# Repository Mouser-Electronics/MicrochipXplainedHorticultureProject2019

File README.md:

# Microchip Xplained Horticulture Project 2019

Horticulture Sensor Project powered by:

- Microchip Xplained Board
- Mikro WiFi 3 Click Board
- Microchip ATSAMD10-based STEMMA soil moisture
- Mikro Weather Click Board temperature and humidity sensor
- DFRobots soil pH sensor
- DFRobots CO2 sensor

BOM: https://www.mouser.com/ProjectManager/ProjectDetail.aspx?AccessID=F9EF1AE298

Project Article: https://www.mouser.com/applications/smarter-green-thumb-powered-by-microchip/

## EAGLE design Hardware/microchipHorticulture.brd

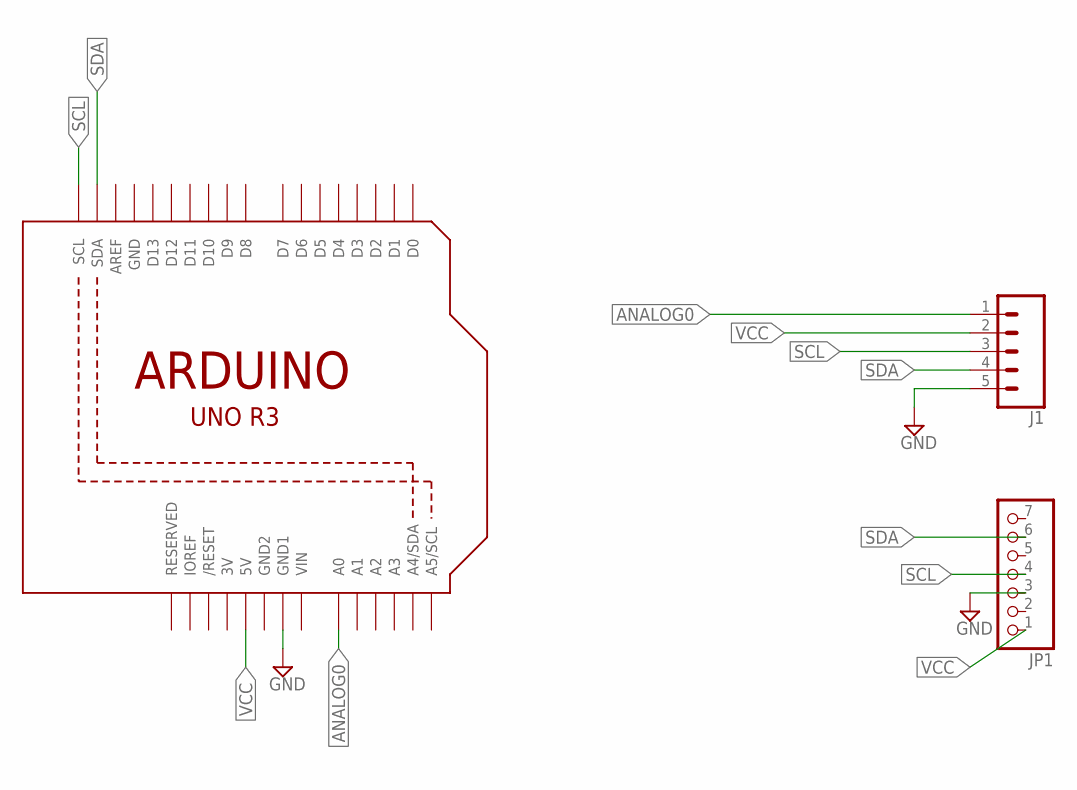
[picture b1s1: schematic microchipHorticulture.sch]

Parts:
J1: CONN_05SCREW; SCREWTERMINAL-3.5MM-5
JP1: PINHD-1X7; 1X07
U1: ARDUINOR3-BPLACE

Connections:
3V: U1.3V
ANALOG0: J1.1, U1.A0
GND: J1.5, JP1.3, U1.GND, U1.GND1
GND2: U1.GND2
SCL: J1.3, JP1.4, U1.SCL
SDA: J1.4, JP1.6, U1.SDA
VCC: J1.2, JP1.1, U1.5V
VIN: U1.VIN

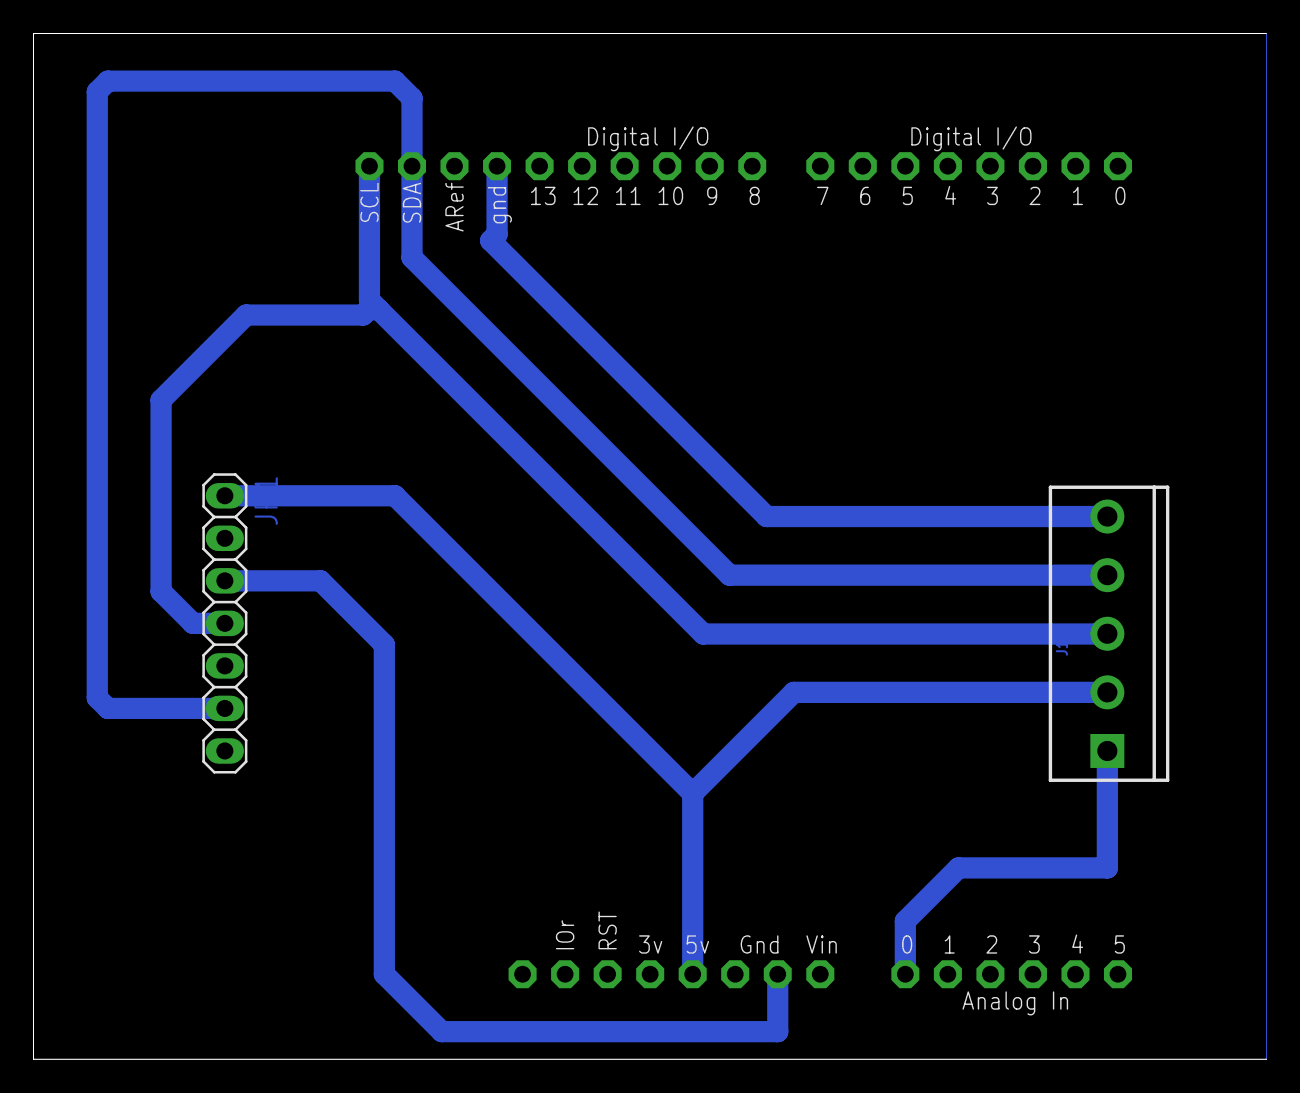
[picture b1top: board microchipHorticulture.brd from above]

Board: 2 copper layers, 73.6 x 61.3 mm, 3 parts (0 on the bottom side), 5 nets.

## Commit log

2019-02-11 init commit
2019-02-13 soft serial for WiFiEsp
2019-02-16 added co2 sensor custom library
2019-02-23 Create function to get pH reading
2019-02-28 revised schematic capture
2019-02-28 added Atmel Studio project files

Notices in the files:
parts and their libraries:
SparkFun-Connectors: Licensing: Creative Commons ShareAlike 4.0 International - https://creativecommons.org/licenses/by-sa/4.0
